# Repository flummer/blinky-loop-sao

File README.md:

# Blinky Loop SAO

Further documentation on the [hackaday.io project page for the Blinky Loop SAO](https://hackaday.io/project/198163-blinky-loop-sao)

Main Components:

- [ST LIS2DH12 - MEMS digital output motion sensor: ultra-low-power high-performance 3-axis "femto" accelerometer with I2C interface](https://www.st.com/en/mems-and-sensors/lis2dh12.html)
    - [datasheet](https://www.st.com/resource/en/datasheet/lis2dh12.pdf)
- [WorldSemi WS2812b-2020 - Addressable RGB LEDs](http://www.world-semi.com/ws2812-family/)
    - [datasheet](https://www.lcsc.com/datasheet/lcsc_datasheet_2012110135_Worldsemi-WS2812B-2020_C965555.pdf)

## Designed in KiCad v8.99 (nightly)

To open the project, you will need to install a recent nightly build (og v9 or newer when released), KiCad v8 or earlier won't open this design directly.

## License

The hardware design of the `main` branch of this repository is released under the following license:

* the "Creative Commons Attribution-ShareAlike 4.0 International License"
  (CC BY-SA 4.0) full text of this license is included in the LICENSE file
  and a copy can also be found at
  [http://creativecommons.org/licenses/by-sa/4.0/](http://creativecommons.org/licenses/by-sa/4.0/)

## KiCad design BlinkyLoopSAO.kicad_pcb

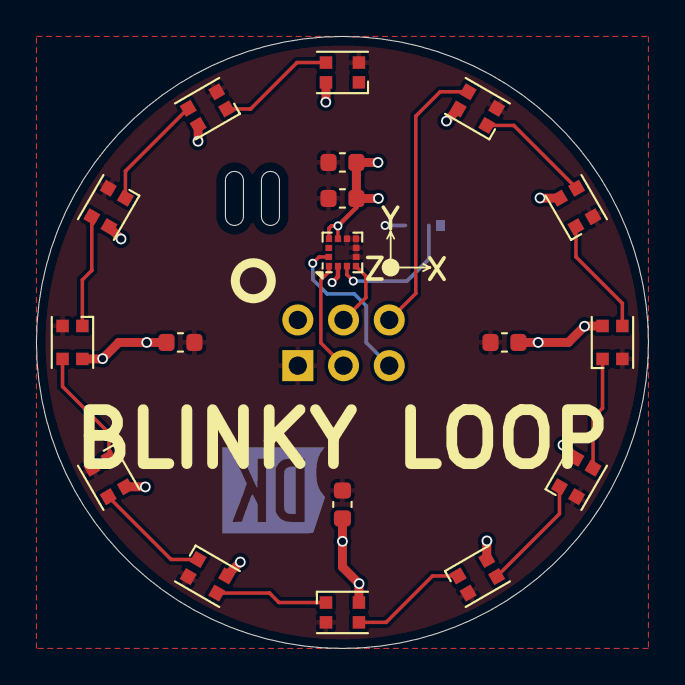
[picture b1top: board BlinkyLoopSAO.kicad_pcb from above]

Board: 2 copper layers, 34.0 x 34.0 mm, 20 parts (1 on the bottom side), 18 nets.

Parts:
C1: 10uF; C_0603_1608Metric
C2, C3, C4, C5: 100nF; C_0603_1608Metric
D1, D2, D3, D4, D5, D6, D7, D8, D9, D10, D11, D12: WS2812B-2020; LED_WS2812B-2020_PLCC4_2.0x2.0mm
JP1: SolderJumper_3_Bridged12; SolderJumper-3_P1.3mm_Bridged12_RoundedPad1.0x1.5mm_NumberL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
U1: LIS2Dx12; LGA-12_2x2mm_P0.5mm
X1: Badgelife_sao_connector_v169bis; Badgelife-SAOv169-SAO-2x3

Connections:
ACC_INT: U1.12 (INT1), X1.6 (GPIO2)
GND: C1.2, C2.2, C3.2, C4.2, C5.2, D1.2 (VSS), D2.2 (VSS), D3.2 (VSS), D4.2 (VSS), D5.2 (VSS), D6.2 (VSS), D7.2 (VSS), D8.2 (VSS), D9.2 (VSS), D10.2 (VSS), D11.2 (VSS), D12.2 (VSS), JP1.3 (B), U1.5 (RES(GND)), U1.6 (GND), U1.7 (GND), U1.8 (GND), X1.2 (GND)
LED_CONTROL: D1.3 (DIN), X1.5 (GPIO1)
unnamed: D1.1 (DOUT), D2.3 (DIN)
unnamed: D2.1 (DOUT), D3.3 (DIN)
unnamed: D3.1 (DOUT), D4.3 (DIN)
unnamed: D4.1 (DOUT), D5.3 (DIN)
unnamed: D5.1 (DOUT), D6.3 (DIN)
unnamed: D6.1 (DOUT), D7.3 (DIN)
unnamed: D7.1 (DOUT), D8.3 (DIN)
unnamed: D8.1 (DOUT), D9.3 (DIN)
unnamed: D9.1 (DOUT), D10.3 (DIN)
unnamed: D10.1 (DOUT), D11.3 (DIN)
unnamed: D11.1 (DOUT), D12.3 (DIN)
unnamed: JP1.2 (C), U1.3 (SDO/SA0)
SCL: U1.1 (SCL/SPC), X1.4 (SCL)
SDA: U1.4 (SDA/SDI/SDO), X1.3 (SDA)
VCC: C1.1, C2.1, C3.1, C4.1, C5.1, D1.4 (VDD), D2.4 (VDD), D3.4 (VDD), D4.4 (VDD), D5.4 (VDD), D6.4 (VDD), D7.4 (VDD), D8.4 (VDD), D9.4 (VDD), D10.4 (VDD), D11.4 (VDD), D12.4 (VDD), JP1.1 (A), U1.2 (CS), U1.9 (VDD), U1.10 (VDD-IO), X1.1 (VCC)

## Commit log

2024-10-15 Added documentation and license
2024-10-15 Fixed typo
